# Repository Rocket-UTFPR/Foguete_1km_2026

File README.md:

# Foguete_1km_2026
Repositório com os códigos e placas da aviônica do foguete de 1km para a LASC de 2026.

# 1. Especificações de requisitos
Segue abaixo especificações dos requisitos

## 1.1 Requisitos de Hardware

Requisitos Não-Funcionais

|Requisito |Descrição |Prioridade |
|----------|----------|-----------|
|RNFH01 |Deve-se usar o microcontrolador ESP32                                                                    |Alta |
|RNFH02 |Todos os componentes não passivos da placa devem ser SMD                                                 |Média|
|RNFH03 |O sistema deve operar no mínimo 2h sem carga                                                             |Média|
|RNFH04 |O alcance da comunicação LoRa deve ser de, no mímino,5km em campo aberto                                 |Alta |
|RNFH05 |O conversor CC-CC não isolado deve ser buck ou Ćuk, projetado pela própria equipe                        |Baixa|
|RNFH06 |A placa deve contar com plano de terra                                                                   |Alta |
|RNFH07 |Deve haver capacitores cerâmicos de desacoplamento de 100nF nos pinos de alimentação de todos os chips   |Alta |
|RNFH08 |Deve haver filtro de debounce nos botões com freqüência de corte de 30kHz                                |Média|
|RNFH09 |Deve haver filtro passa-baixa RC com freqüência de corte entre 20kHz e 100kHz nos barramentos UART       |Baixa|

Requisitos Funcionais

|Requsito |Descrição |Prioridade |
|---------|----------|-----------|
|RFH01 | O microcontrolador deve transmitir dados de GPS para base via LoRa                                |Alta  |
|RFH02 | O microcontrolador deve gravar dados de altitude no cartão SD                                     |Média |
|RFH03 | A placa de circuito impresso deve ter botões de reset e boot                                      |Média |
|RFH04 | A bateria deve ser conectada à PCB por um RBF (Remove Before Flight)                              |Alta  |
|RFH05 | O microcontrolador deve medir dados de altitude por barômetro e captar localização por GPS        |Alta  |
|RFH06 | Um conversor CC-CC não isolado deve interfacear a bateria com o sistema, tensão de saída de 5V    |Alta  |

# 1.2 Requisitos de Software

Requisitos Não-Funcionais

|Requisito |Descrição |Prioridade |
|----------|----------|-----------|
|RNFS01 |O código deve ser implementado em C++ com o framework Arduino                                            |Alta |
|RNFS02 |A implementação deve fazer uso do sistema operacional FreeRTOS                                           |Alta |
|RNFS03 |Deve haver uma task para captação de dados e acionamento de paraquedas e uma para gravação e transmissão |Alta |

Requisitos Funcionais

|Requisito |Descrição |Prioridade |
|----------|----------|-----------|
|RFS01 | O microcontrolador deve acionar paraquedas após apogeu                                                  |Alta  |
|RFS02 | Deve ser possível gravar código OTA, com página web estilizada                                          |Média |
|RFS03 | Deve haver um wifi-manager que permita ao usuario enviar credenciais de wifi em tempo de execução       |Média |

# 2. Medidas da Placa
- Diâmetro (máximo): 98mm
- Comprimento (máximo): 230mm

# 3. Bugs conhecidos

- No esquemático, a trilha VBUS do USB está conectada à trilha 3V3. A alimentação padrão do USB é de 5V, esse curto-circuito queimaria os componentes da placa;
* Correção: trilhas de VBUS raspadas na versão de voo, jumpeadas para entrada do buck

- No .brd, o sinal diferencial do USB não está roteado corretamente.
* Correção: trilhas jumpeadas com par trançado

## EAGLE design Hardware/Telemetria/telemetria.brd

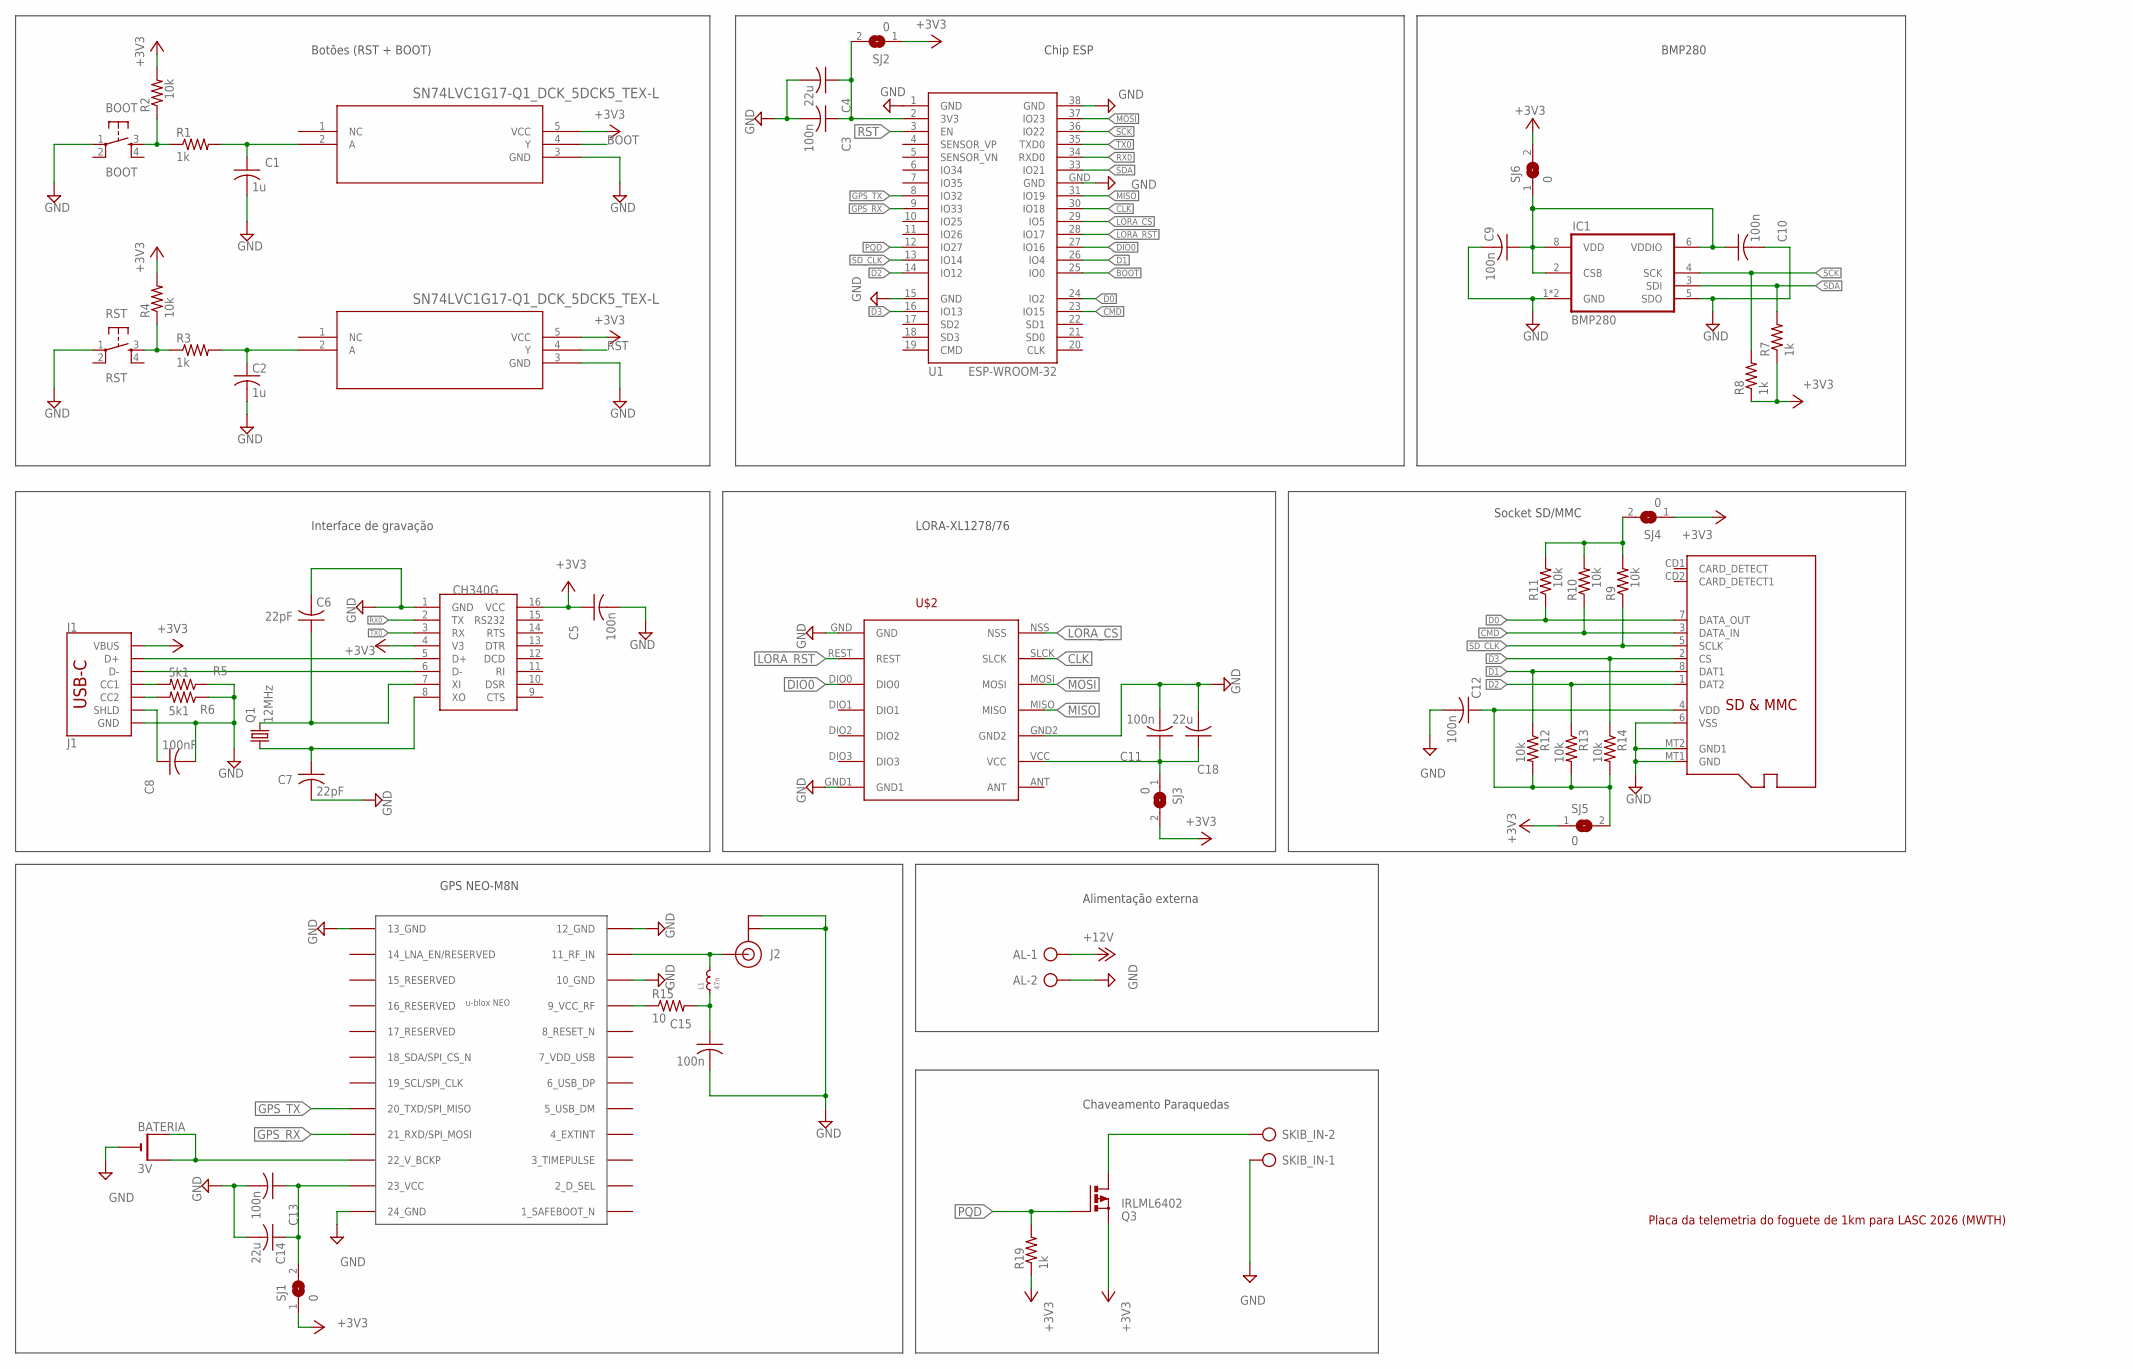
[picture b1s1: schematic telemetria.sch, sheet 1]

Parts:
AL: AL; AK500/2-H
BATERIA: 3V; CR2032-THRU
BOOT: BOOT; TACTILE-PTH
C1, C2: 1u; C3216
C3, C5, C9, C10, C11, C12, C13, C15: 100n; C3216
C4, C14, C18: 22u; C3216
C6, C7: 22pF; C3216
C8: 100nF; C3216
IC1: BMP280
J1: J1; USB-C-16P-2LAYER-PADS
J2: U.FL
L1: 47n; 0402
Q1: 12MHz; HC49/S
Q3: IRLML6402; SOT-23
R1, R3, R7, R8, R19: 1k; R1206
R2, R4, R9, R10, R11, R12, R13, R14: 10k; R1206
R5, R6: 5k1; R1206
R15: 10; R1206
RST: RST; TACTILE-PTH
SCHMITT-1, SCHMITT-2: SN74LVC1G17-Q1_DCK_5DCK5_TEX-L; DCK5_TEX-L
SJ1, SJ2, SJ3, SJ4, SJ5, SJ6: 0; SJ
SKIB_IN: SKIB; AK500/2-H
U1: ESP-WROOM-32
U$1: CH340G; SOIC16
U$2: LORA; LORAXL1276/78
U$3: MICROSD
U$4: NEO-M8

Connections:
3V3: R9.2, R10.2, R11.2, SJ4.2
3V3_GPS: C13.1, C14.1, SJ1.2, U$4.23 (23_VCC)
+3V3: C5.1, J1.VBUS1 (VBUS), J1.VBUS2 (VBUS), Q3.P2 (S), R2.2, R4.2, R7.1, R8.1, R19.1, SCHMITT-1.5 (VCC), SCHMITT-2.5 (VCC), SJ1.1, SJ2.1, SJ3.2, SJ4.1, SJ5.1, SJ6.2, U$1.4 (V3), U$1.16 (VCC); also elsewhere on the board
+12V: AL.1; also elsewhere on the board
BOOT: SCHMITT-1.4 (Y), U1.25 (IO0)
CLK: U1.30 (IO18), U$2.SLCK
CMD: R10.1, U1.23 (IO15), U$3.3 (DATA_IN)
D0: R11.1, U1.24 (IO2), U$3.7 (DATA_OUT)
D1: R12.1, U1.26 (IO4), U$3.8 (DAT1)
D2: R13.1, U1.14 (IO12), U$3.1 (DAT2)
D3: R14.1, U1.16 (IO13), U$3.2 (CS)
DIO0: U1.27 (IO16), U$2.DIO0
ESP_VCC: C3.1, C4.1, SJ2.2, U1.2 (3V3)
GND: AL.2, BOOT.1, C1.2, C2.2, C3.2, C4.2, C5.2, C6.2, C7.2, C8.2, C9.2, C10.2, C11.2, C12.2, C13.2, C14.2, C15.2, C18.2, IC1.1 (GND), IC1.5 (SDO), IC1.7 (GND), J1.GND, J1.GND2 (GND), J2.1 (GND), J2.2 (GND), R5.1, R6.1, RST.1, SCHMITT-1.3 (GND), SCHMITT-2.3 (GND), SKIB_IN.1, U1.1 (GND), U1.15 (GND), U1.38 (GND), U1.GND, U$1.1 (GND), U$2.GND, U$2.GND1, U$2.GND2, U$3.6 (VSS), U$3.MT1 (GND), U$3.MT2 (GND1), U$4.10 (10_GND), U$4.12 (12_GND), U$4.13 (13_GND); also elsewhere on the board
GPS_RX: U1.9 (IO33), U$4.21 (21_RXD/SPI_MOSI)
GPS_TX: U1.8 (IO32), U$4.20 (20_TXD/SPI_MISO)
LORA_CS: U1.29 (IO5), U$2.NSS
LORA_RST: U1.28 (IO17), U$2.REST
MISO: U1.31 (IO19), U$2.MISO
MOSI: U1.37 (IO23), U$2.MOSI
unnamed: BOOT.3, R1.1, R2.1
unnamed: C1.1, R1.2, SCHMITT-1.2 (A)
unnamed: R3.1, R4.1, RST.3
unnamed: C2.1, R3.2, SCHMITT-2.2 (A)
unnamed: C7.1, Q1.1, U$1.8 (XO)
unnamed: C6.1, Q1.2, U$1.7 (XI)
unnamed: C8.1, J1.SHLD1 (SHLD), J1.SHLD2 (SHLD), J1.SHLD3 (SHLD), J1.SHLD4 (SHLD)
unnamed: J1.A5 (CC1), R5.2
unnamed: J1.B5 (CC2), R6.2
unnamed: BATERIA.-, U$4.24 (24_GND)
unnamed: J2.FEED (SIGNAL), L1.2, U$4.11 (11_RF_IN)
unnamed: C15.1, L1.1, R15.2
unnamed: R15.1, U$4.9 (9_VCC_RF)
unnamed: BATERIA.+1 (+), BATERIA.+2 (+1), U$4.22 (22_V_BCKP)
unnamed: C11.1, C18.1, SJ3.1, U$2.VCC
unnamed: Q3.P3 (D), SKIB_IN.2
PQD: Q3.P1 (G), R19.2, U1.12 (IO27)
RST: SCHMITT-2.4 (Y), U1.3 (EN)
RX0: U1.34 (RXD0), U$1.2 (TX)
SCK: IC1.4 (SCK), R8.2, U1.36 (IO22)
SDA: IC1.3 (SDI), R7.2, U1.33 (IO21)
SD_CLK: R9.1, U1.13 (IO14), U$3.5 (SCLK)
SJ_3V3: C9.1, C10.1, IC1.2 (CSB), IC1.6 (VDDIO), IC1.8 (VDD), SJ6.1
TX0: U1.35 (TXD0), U$1.3 (RX)
USBD_N: J1.A7 (D-), J1.B7 (D-), U$1.6 (D-)
USBD_P: J1.A6 (D+), J1.B6 (D+), U$1.5 (D+)
VDD: C12.1, R12.2, R13.2, R14.2, SJ5.2, U$3.4 (VDD)

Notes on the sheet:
Botões (RST + BOOT)
Interface de gravação
Chip ESP
BMP280
LORA-XL1278/76
Socket SD/MMC
GPS NEO-M8N
Chaveamento Paraquedas
Alimentação externa
Placa da telemetria do foguete de 1km para LASC 2026 (MWTH)

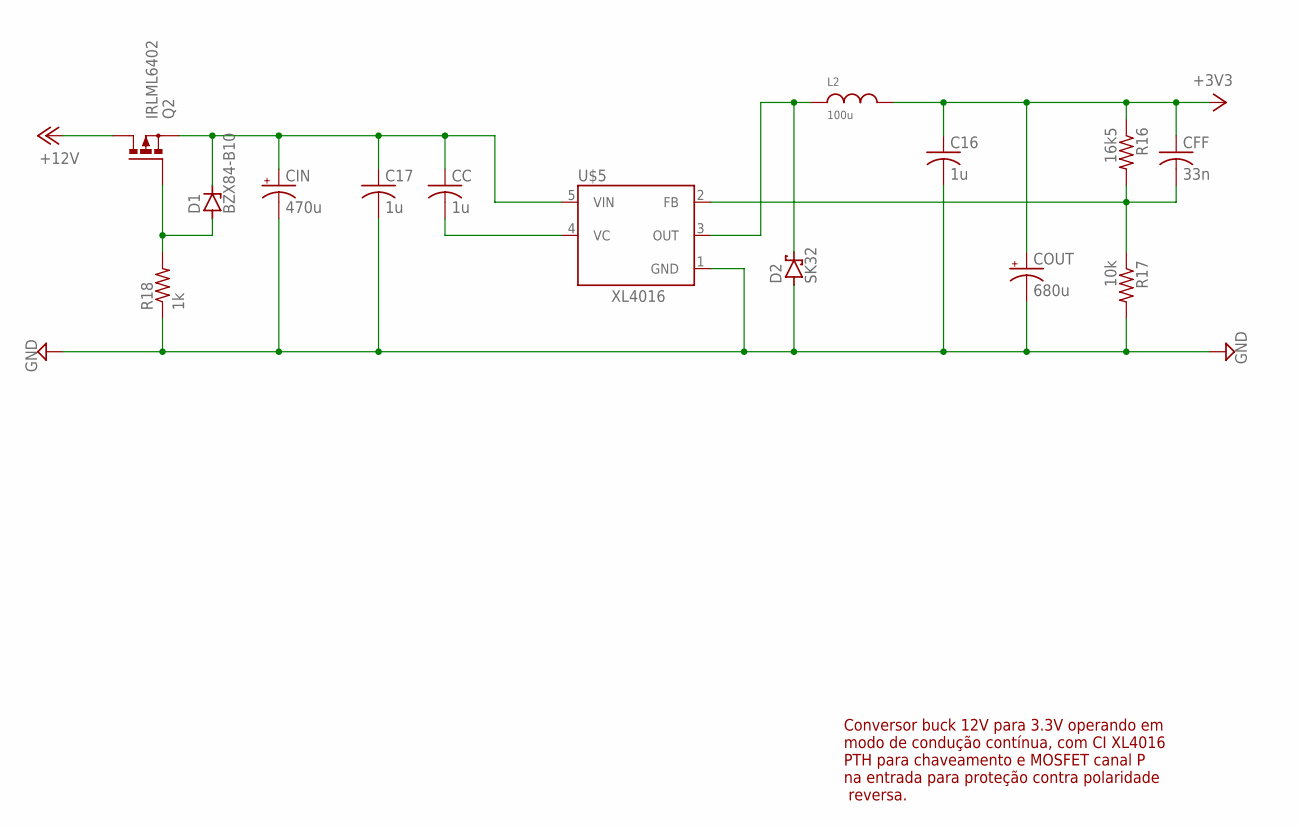
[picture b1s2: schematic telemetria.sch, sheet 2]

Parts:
C16, C17: 1u; C1206
CC: 1u; C1206
CFF: 33n; C1206
CIN: 470u; E3,5-8
COUT: 680u; E3,5-8
D1: BZX84-B10; SOT23
D2: SK32; SMC
L2: 100u; INDUTOR_125125
Q2: IRLML6402; SOT-23
R16: 16k5; R1206
R17: 10k; R1206
R18: 1k; M1206
U$5: XL4016; LM2576T2

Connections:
+3V2: C17.1, CC.1, CIN.+, D1.3 (C), Q2.P2 (S), U$5.5 (VIN)
+3V3: C16.1, CFF.1, COUT.+, L2.P$2, R16.1; also elsewhere on the board
+12V: Q2.P3 (D); also elsewhere on the board
BYPASS: CC.2, U$5.4 (VC)
FB: CFF.2, R16.2, R17.1, U$5.2 (FB)
GND: C16.2, C17.2, CIN.-, COUT.-, D2.A, R17.2, R18.1, U$5.1 (GND); also elsewhere on the board
unnamed: D1.1 (A), Q2.P1 (G), R18.2
SWOUT: D2.C, L2.P$1, U$5.3 (OUT)

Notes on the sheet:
Conversor buck 12V para 3.3V operando em modo de condução contínua, com CI XL4016 PTH para chaveamento e MOSFET canal P na entrada para proteção contra polaridade reversa.

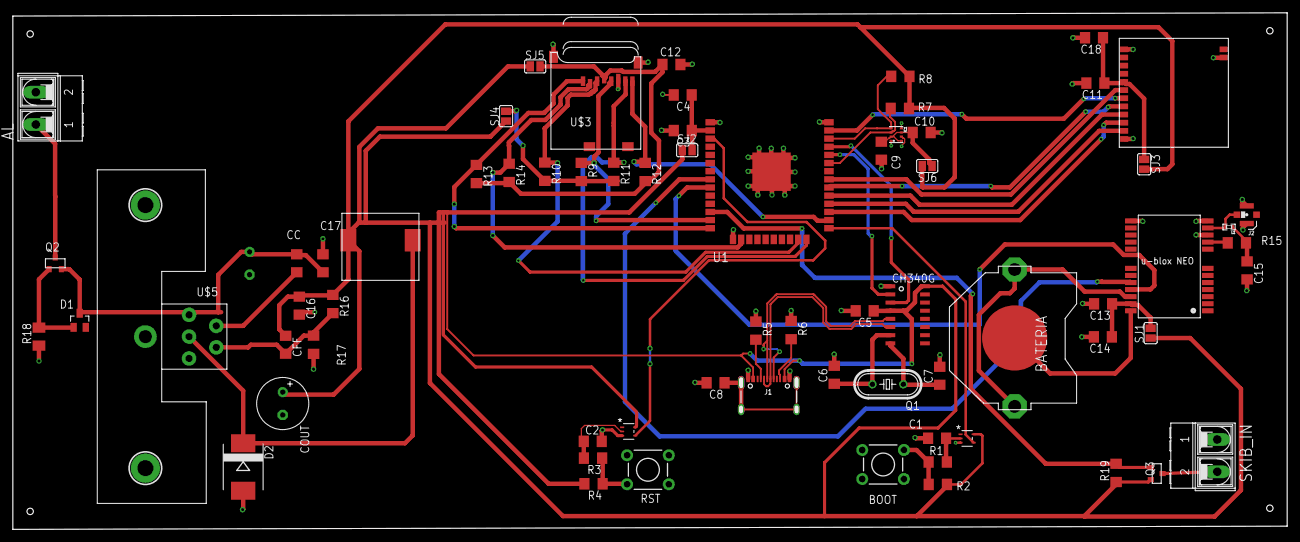
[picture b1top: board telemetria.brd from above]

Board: 2 copper layers, 198.0 x 79.9 mm, 70 parts (1 on the bottom side), 52 nets.

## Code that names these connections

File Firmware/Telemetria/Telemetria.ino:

/*******************************************************
Código da placa principal do foguete de 1km para a LASC

Código para ESP32 Dev Module

Início: 2026/01
Término: 2026/02

Requisitos implementados:

Aquisição de dados com BMP280
Transmissão de dados com LoRa XL1278
Gravação de dados com socket SDMMC

Core 0: aquisição de sensores
Core 1: transmissão via LoRa
        gravação SD
Escalonamento por afinidade implementado com FreeRTOS
Comunicação por fila FreeRTOS

To-do:

Atualização de código OTA
Captação e envio de dados GPS
Core 0: Acionamento de paraquedas

Atualização de código OTA será necessário, porque alguns
pinos do socket do SD são usados como bootstrapping

Convenções de nomenclatura:

t_  : funções de tasks
qh_ : handles de filas RTOS
th_ : handles de tasks RTOS
f   : flags booleanas
x   : BaseType_t RTOS 

Convenções para nomes de arquivos:

/flight.txt : dados de voo/telemetria
/wifi.txt   : credenciais wifi (NUNCA deixar hardcoded)
/static.txt : dados de teste estático
********************************************************/

/*** Cabeçalho ***/
#include <HardwareSerial.h>
#include <SPI.h>
#include <Adafruit_BMP280.h>
#include <LoRa.h>
#include <TinyGPSPlus.h>
#include <SD_MMC.h>

#define LORA_SS 5 
#define LORA_RST 17
#define LORA_DIO0 16
#define GPS_RX 33 // RX do ESP, TX do GPS
#define GPS_TX 32 // TX do ESP, RX da GPS
#define PIN_PARAQUEDAS 27


#define ERROR_LOG(msg) \
   do{ \
    Serial.println(msg); \
   } while(0) //Do-while para evitar bugs


Adafruit_BMP280 bmp = Adafruit_BMP280();
SPIClass lora_spi(VSPI);
TinyGPSPlus gps;
HardwareSerial gpsSerial(2);

uint32_t pacotesPerdidos = 0;
float altIni = 0;
volatile float altAtual = 0,
               altAnterior = 0;

enum class EtapasVoo{
  SOLO,
  VOO,
  QUEDA,
  PARAQUEDAS
};
volatile EtapasVoo etapaAtual = EtapasVoo::SOLO;

struct dadosTelemetria{
  float altitude;
  //double latitude,
  //       longitude;
  //bool newGpsData;
  unsigned long uptime;
};

TaskHandle_t th_captacaoDados = NULL,
             th_transmissaoDados = NULL,
             th_ejecao = NULL;
QueueHandle_t qh_dadosAltitude = NULL;

void t_captacaoDados(void *pvParameters);
void t_transmissaoDados(void *pvParameters);
void t_ejecao(void *pvParameters);

void setup() {
  File arquivo = File();

  Serial.begin(115200);

  pinMode(PIN_PARAQUEDAS, OUTPUT);
  digitalWrite(PIN_PARAQUEDAS, HIGH);

  //gpsSerial.begin(9600, SERIAL_8N1, GPS_RX, GPS_TX);

  if(!bmp.begin(0x76)) ERROR_LOG("Erro: BMP não iniciado");
  else{
    bmp.setSampling(Adafruit_BMP280::MODE_NORMAL, // modo de operação
                  Adafruit_BMP280::SAMPLING_X2, // temperatura
                  Adafruit_BMP280::SAMPLING_X16, // pressão
                  Adafruit_BMP280::FILTER_X16, //filtro de correção de dados
                  Adafruit_BMP280::STANDBY_MS_1);
    altIni = bmp.readAltitude(1013.25);
  }
  if(!SD_MMC.begin()){ ERROR_LOG("Erro: cartão SD não iniciado"); }
  arquivo = SD_MMC.open("/flight.txt", FILE_WRITE);
  if(!arquivo){ ERROR_LOG("Erro: arquivo não aberto");}
  arquivo.close();



  /*************************** Tabela de alcance LoRa (empírica) ***************************
  SF | BW (kHZ) | Velocidade aproximada (kbps) | Alcance campo aberto | Alcance urbano
  6  | 500      |              ~25             |       500m - 1km     | 100m - 300m
  7  | 125      |              ~9              |       1km - 2 km     | 300m - 800m
  8  | 125      |              ~4.5            |       2km - 4km      | 400m - 1.2km
  9  | 125      |              ~2              |       3km - 6km      | 500m - 2km
  10 | 125      |              ~1              |       5km - 8km      | 700m - 3km
  11 | 62.5     |              ~0.5            |       7km - 12km     | 1km - 4km
  12 | 31.25    |              ~0.25           |      10km - 15+ km   | 2km - 5km
  *************************** Usar para configurar parâmetros LoRa *************************/

  LoRa.setSPI(lora_spi);
  LoRa.setPins(LORA_SS, LORA_RST, LORA_DIO0);
  if(!LoRa.begin(915e6)){ ERROR_LOG("Erro: LoRa não iniciado"); }
  LoRa.setSyncWord(0xFE);
  LoRa.setSpreadingFactor(11);
  LoRa.setSignalBandwidth(62.5e3);

  qh_dadosAltitude = xQueueCreate(2048, sizeof(dadosTelemetria));

  if(xTaskCreatePinnedToCore(
    t_captacaoDados,
    "Captacao de dados",
    5000,
    NULL,
    1,
    &th_captacaoDados,
    0
  ) == pdFALSE){ 
    ERROR_LOG("Erro: task \'Captacao de dados\' não iniciada"); 
  }

  if(xTaskCreatePinnedToCore(
    t_transmissaoDados,
    "Transmissao de dados",
    6000,
    NULL,
    1,
    &th_transmissaoDados,
    1
  ) == pdFALSE){ 
    ERROR_LOG("Erro: task \'Trasmissao de dados\' não iniciada");
  }

  if(xTaskCreatePinnedToCore(
    t_ejecao,
    "Ejeção do paraquedas",
    2000,
    NULL,
    2,
    &th_ejecao,
    tskNO_AFFINITY
  ) == pdFALSE){ 
    ERROR_LOG("Erro: task \'Ejeção do paraquedas\' não iniciada"); 
  }
}

void loop() {
  vTaskDelete(NULL);
}

/*** Declaração de tasks ***/

void t_captacaoDados(void *pvParameters){
  struct dadosTelemetria dados = {};
  BaseType_t xDadosFilaEnviados = pdFALSE;
  String payloadTelemetria = ""; 
  File arquivo = SD_MMC.open("/flight.txt", FILE_APPEND);
  

  while(1){
    dados.uptime = millis();
    dados.altitude = bmp.readAltitude(1013.25) - altIni;
    //dados.newGpsData = false;
    altAnterior = altAtual;
    altAtual = dados.altitude;

    payloadTelemetria = String(dados.altitude) + ";" 
                      //+ String(dados.latitude, 6) + ";"
                      //+ String(dados.longitude, 6) + ";"
                      //+ String(pacotesPerdidos) + ";"
                      //+ String(dados.newGpsData) + ";"
                      + String(dados.uptime) +
                      ("\0");
    
    if(arquivo){
      arquivo.println(payloadTelemetria);
      arquivo.flush();
      Serial.println("Gravou no SD..");

      if ((etapaAtual == EtapasVoo::SOLO) && (digitalRead(PIN_PARAQUEDAS) == LOW)) {
        arquivo.close();
      }
    } else {
      Serial.println("Erro: arquivo não aberto no SD");
    }
    
    /*
    while(gpsSerial.available()){
      Serial.println("porta recebeu");
      if(gps.encode(gpsSerial.read())){
        Serial.println("String válida lida");
        if(gps.location.isValid()){
          Serial.println("location valid");
          dados.latitude = gps.location.lat();
          dados.longitude = gps.location.lng();
          dados.newGpsData = true;
        }
      }
    }*/

    xDadosFilaEnviados = xQueueSend(qh_dadosAltitude, &dados, pdMS_TO_TICKS(5));

    if(xDadosFilaEnviados == pdFALSE) pacotesPerdidos++;

    vTaskDelay(pdMS_TO_TICKS(20));
  }
}

void t_transmissaoDados(void *pvParameters){
  uint8_t fLoraDisponivel = 0;
  struct dadosTelemetria dados = {};
  BaseType_t xDadosFilaRecebidos = pdFALSE;
  String payloadTelemetria = "";

  while(1){
    xDadosFilaRecebidos = xQueueReceive(qh_dadosAltitude, &dados, portMAX_DELAY);
    Serial.println(altAtual);
    //Serial.println(dados.longitude);
    //Serial.println(dados.latitude);

    if(xDadosFilaRecebidos == pdTRUE){
      payloadTelemetria = String(dados.altitude) + ";" 
                          //+ String(dados.latitude, 6) + ";"
                          //+ String(dados.longitude, 6) + ";"
                          //+ String(pacotesPerdidos) + ";"
                          //+ String(dados.newGpsData) + ";"
                          + String(dados.uptime) +
                          ("\0");

      fLoraDisponivel = LoRa.beginPacket();
      
      if(fLoraDisponivel == 1){
        LoRa.print(payloadTelemetria);
        LoRa.endPacket();
      } else{
        Serial.println("LoRa indisponível");
      }
    }
  }
}

 // Função de Ejeção do Paraquedas
void t_ejecao (void *pvParameters){

  int contQueda = 0;
  int contRuido = 0;

  while(1){
    switch (etapaAtual) {
    case EtapasVoo::SOLO:
      Serial.println("SOLO");
      if (altAtual > 120) etapaAtual = EtapasVoo::VOO;

      break;

    case EtapasVoo::VOO:
      Serial.println("VOO");
      contQueda = 0;
      contRuido = 0;
      if (altAtual < altAnterior) etapaAtual = EtapasVoo::QUEDA;

      break;

    case EtapasVoo:: QUEDA:
      Serial.println("QUEDA");
      if (altAtual < altAnterior){
        contQueda++;
        Serial.println(contQueda);

        //if(contQueda >= 9) break;
      }
      if (altAtual > altAnterior){
        contRuido++;
        Serial.println(contRuido);
      }

      if (contRuido >= 3) etapaAtual = EtapasVoo::VOO;
      if (contQueda >= 9) etapaAtual = EtapasVoo::PARAQUEDAS;
      break;

    case EtapasVoo::PARAQUEDAS:
      digitalWrite(PIN_PARAQUEDAS, LOW);
      Serial.println("PARAQUEDAS ACIONADO");
      if (altAtual < 120) etapaAtual = EtapasVoo::SOLO;
      break;
    
    default:
      ERROR_LOG("Estado não esperado na ejeção do paraquedas");
      etapaAtual = EtapasVoo::SOLO;
      break;
    }
    vTaskDelay(pdMS_TO_TICKS(20));
  }
}

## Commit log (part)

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2026-04-30 Teste
    Testandoooo
2026-04-30 Adição inicial de requisitos não-funcionais
    Adição dos requisitos não funcionais da placa de telemetria
2026-04-30 Create a
2026-04-30 Add initial content to Hardware/a
2026-04-30 codigo inicial da telemetria
2026-05-07 integração do bmp
2026-05-07 sd feito
2026-05-22 qualquer coisa
2026-05-22 lora adicionado, não testado
2026-05-22 adicionado contador de pacotes perdidos
2026-05-25 log de debug, adaptado para SD SMD. Necessita testes
2026-05-25 comentários
2026-05-26 Add new requirements to README
2026-05-28 commit de seguranca
2026-05-28 gps alpha
2026-05-29 gps beta
2026-05-29 Update hardware and software requirements in README
2026-06-02 Medidas físicas adicionadas ao Read-me
    Added section for board measurements.
2026-06-12 inicio do standalone do ESP32
2026-06-12 gps e delay
2026-06-18 bmp280
2026-06-26 SD e LoRa no hardware

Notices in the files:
parts and their libraries:
SparkFun-Retired: Licensing: Creative Commons ShareAlike 4.0 International - https://creativecommons.org/licenses/by-sa/4.0
esp32: Creative Commons Attribution-ShareAlike 4.0 International
COPYRIGHT: Copyright (C) 2026 Ultra Librarian. All rights reserved.
